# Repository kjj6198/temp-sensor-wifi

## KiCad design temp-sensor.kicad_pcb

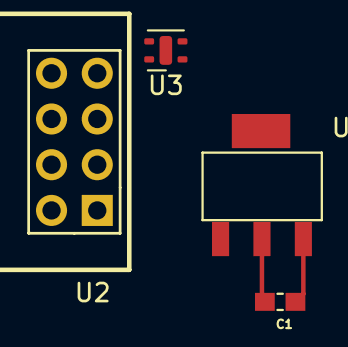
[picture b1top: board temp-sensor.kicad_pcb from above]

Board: 2 copper layers, 5 parts (0 on the bottom side), 4 nets.

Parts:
BT1: Battery_Cell; Battery_CR1225
C1: 0.1uF; CAPC1608X90
U1: TC1262-33; SOT-223-3
U2: ESP-01v090; ESP-01
U3: SHTC3; Sensirion_DFN-4-1EP_2x2mm_P1mm_EP0.7x1.6mm

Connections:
+3V3: C1.1, U1.3, U2.7, U3.4
GND: C1.2, U1.2, U2.2, U3.1
SCL: U2.6, U3.2
SDA: U2.4, U3.3

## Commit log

2021-11-30 first init and scheme design
2021-11-30 remove attiny85 (use esp01)
2021-11-30 update footprint
2021-12-01 add missing footprint
